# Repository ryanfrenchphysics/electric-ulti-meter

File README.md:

# Ulti-Meter
All files associated with my current project, the Ulti-Meter. A many-in-one tool to replace the multiple tools that an electrician must use while on the job.

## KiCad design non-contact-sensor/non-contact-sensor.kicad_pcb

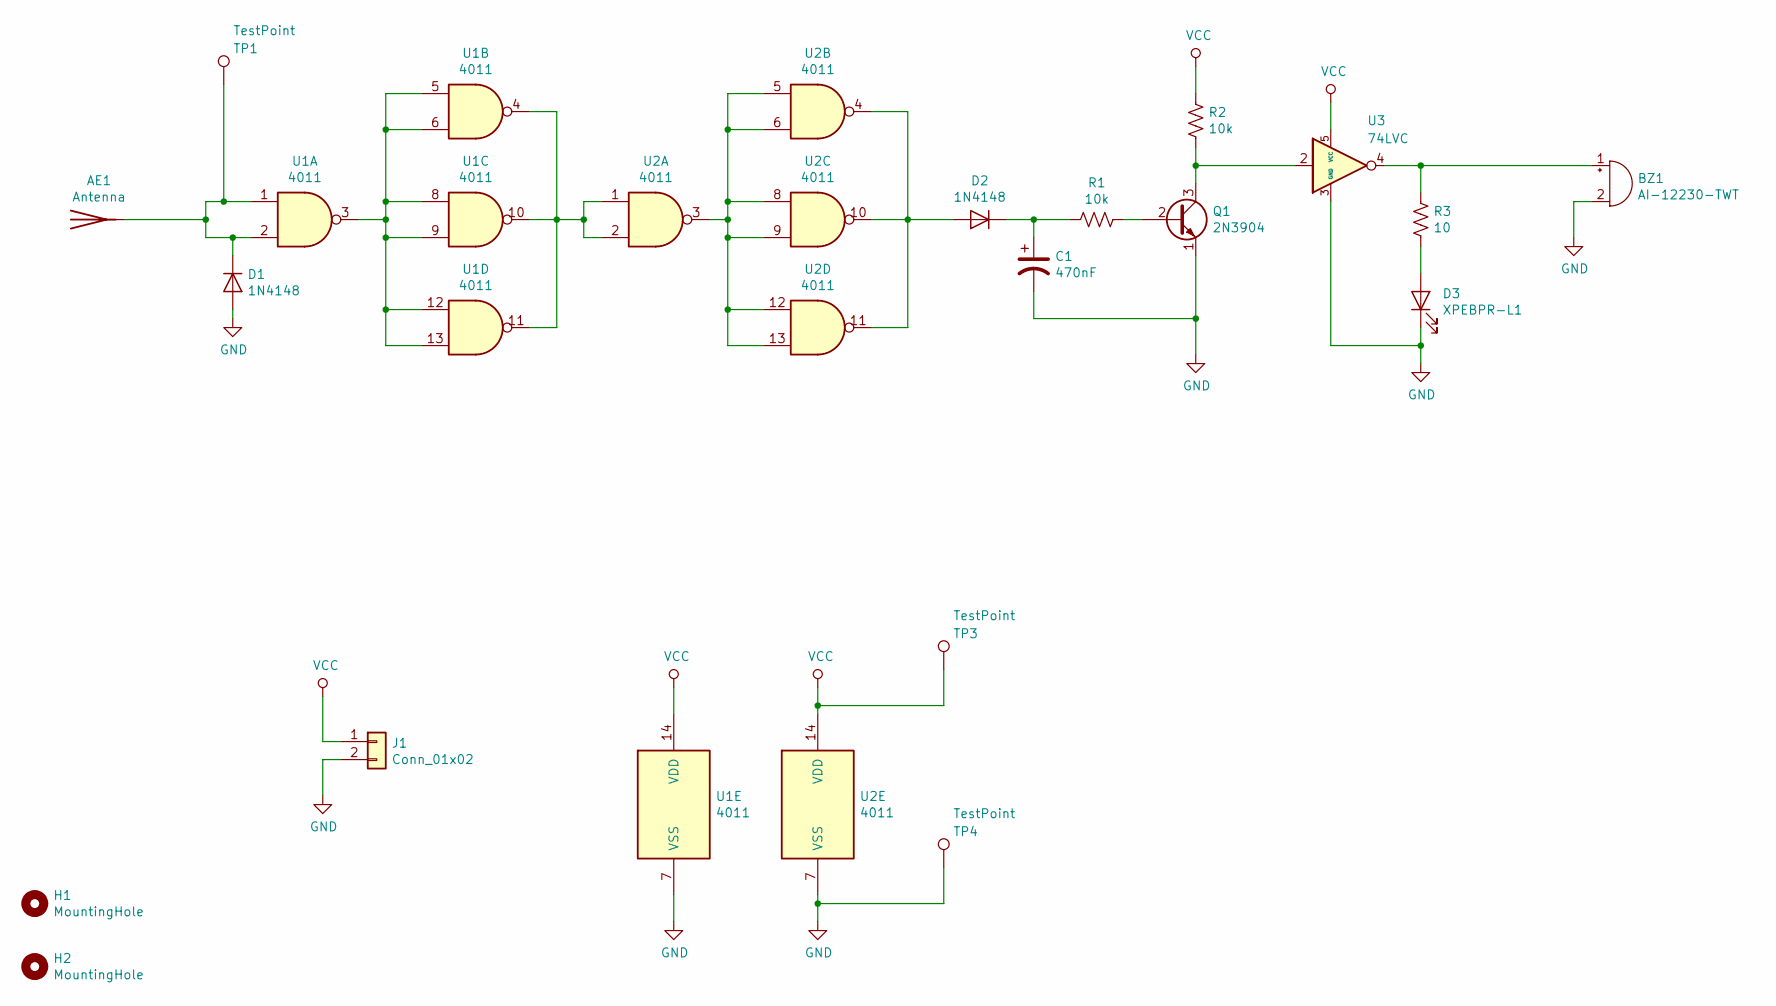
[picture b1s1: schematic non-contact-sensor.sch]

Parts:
AE1: Antenna; TestPoint_Pad_1.0x1.0mm
BZ1: AI-12230-TWT; Buzzer_12x9.5RM7.6
C1: 470nF; C_0603_1608Metric
D1, D2: 1N4148; D_SOD-323
D3: XPEBPR-L1; XPEBPR
H1, H2: MountingHole; MountingHole_2.2mm_M2
J1: Conn_01x02; Molex_Nano-Fit_105313-xx02_1x02_P2.50mm_Horizontal
Q1: 2N3904; SOT-23
R1, R2: 10k; R_0603_1608Metric
R3: 10; R_0603_1608Metric
TP1, TP3, TP4: TestPoint; TestPoint_THTPad_D2.0mm_Drill1.0mm
U1, U2: 4011; TSSOP-14_4.4x5mm_P0.65mm
U3: 74LVC; SOT-553

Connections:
GND: BZ1.2 (+), C1.2, D1.2 (A), D3.1 (K), J1.2, Q1.1 (E), TP4.1, U1.7 (VSS), U2.7 (VSS), U3.3 (GND)
unnamed: AE1.1, D1.1 (K), TP1.1, U1.1, U1.2
unnamed: BZ1.1 (-), R3.2, U3.4
unnamed: C1.1, D2.1 (K), R1.2
unnamed: D2.2 (A), U2.4, U2.10, U2.11
unnamed: D3.2 (A), R3.1
unnamed: Q1.2 (B), R1.1
unnamed: Q1.3 (C), R2.2, U3.2
unnamed: U1.4, U1.10, U1.11, U2.1, U2.2
unnamed: U1.3, U1.5, U1.6, U1.8, U1.9, U1.12, U1.13
unnamed: U2.3, U2.5, U2.6, U2.8, U2.9, U2.12, U2.13
VCC: J1.1, R2.1, TP3.1, U1.14 (VDD), U2.14 (VDD), U3.5 (VCC)

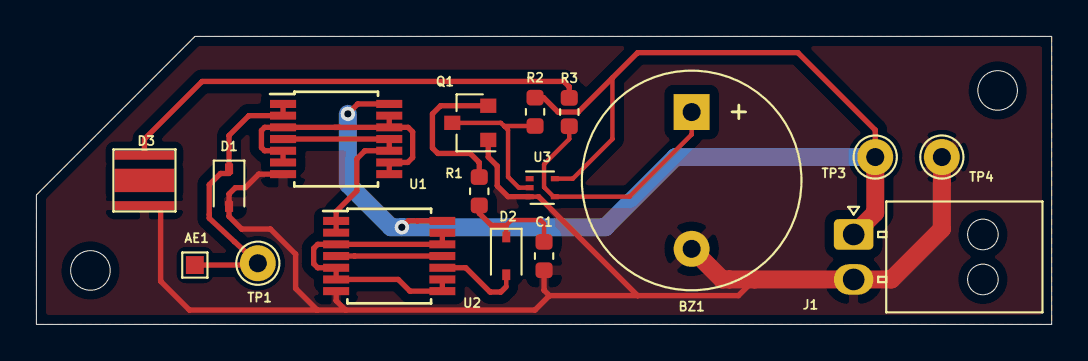
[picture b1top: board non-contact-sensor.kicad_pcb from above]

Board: 2 copper layers, 56.4 x 16.0 mm, 19 parts (0 on the bottom side), 12 nets.

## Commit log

2021-02-06 First commit: Added all current files, including fully-updated non-contact sensor schematic and board files.
2021-02-07 Added a parts list, updated with parts for non-contact AC voltage sensor. Started work on front-end circuit, which will be used for controlling both input from manual buttons and a monochrome eInk sc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
